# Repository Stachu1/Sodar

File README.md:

# Sodar: FPGA-Based Ultrasonic Phased Array

Sodar is a semester project exploring directional ultrasonic object detection using a custom 19-element phased array. The system combines a custom PCB, a Digilent Zedboard with Xilinx Zynq-7000 SoC, VHDL-based signal generation, C firmware running on the Zynq processing system, and a Python visualization tool.

The project was developed as a concept and experimental prototype rather than a finished sensing system. The main goals were to learn the Zynq-7000 architecture and its peripherals, investigate phased-array beam steering, and build a complete hardware-to-software signal path.

## System Overview

The system consists of four main parts:

- **19-element transmitter array** using 40 kHz piezoelectric ultrasonic transducers
- **Custom PCB** with 19 full H-bridge driver channels based on TC78H621FNG motor-driver ICs for driving the transducers
- **Digilent Zedboard (Zynq-7000 SoC)**, with VHDL logic in the programmable logic (PL) generating the phase-shifted transmit signals and C firmware running on the processing system (PS) handling acquisition and signal processing
- **Python host software** for receiving processed data over UART and visualizing the measured echo strength as a function of angle and distance

The system was able to detect a small object at distances of up to approximately 4 m when transmitting straight ahead. When steering the beam towards ±20°, the received signal became substantially weaker and more affected by noise, limiting reliable detection of the test object to approximately 1 m.

## Transducer Array

The array contains 19 identical 40 kHz ultrasonic transducers arranged in two staggered rows: one row contains 10 transducers and the other contains 9.

The physical spacing between adjacent transducers along each row is 10 mm. The second row is shifted by 5 mm, creating a staggered arrangement where the projected spacing between elements along the left-right steering axis is approximately 5 mm.

At 40 kHz, the acoustic wavelength in air is approximately 8.6 mm at room temperature, making the projected element spacing close to λ/2. The arrangement was chosen for horizontal beam steering while keeping the projected element spacing small enough to reduce unwanted grating lobes.

The array was designed for horizontal steering only; there is no intended vertical beam steering.

A 3D radiation pattern simulation was used to visualize the array's predicted transmission characteristics and beam steering performance.

## Hardware

The custom PCB contains the 19 ultrasonic transducers together with the electronics required to drive them.

Each transducer has an independent H-bridge output provided by a motor-driver IC (TC78H621FNG). The Zynq PL provides the control signals required for each channel, including an enable signal and drive-direction signals.

The board was designed, assembled, and soldered as part of the project.

Main hardware:

- Digilent ZedBoard with Xilinx Zynq-7000 SoC
- 19 - 40 kHz ultrasonic transducers
- 19 - full H-bridge driver channels
- Custom PCB with transducers and driver ICs (TC78H621FNG)
- Zynq-7000 internal XADC used for receiving the ultrasonic signal

## FPGA and Firmware

The Zynq-7000 is divided into two parts in the project:

- **Programmable Logic (PL):** VHDL implementation of the phase-controlled transmit signal generation
- **Processing System (PS):** C firmware running on the Zynq CPU for ADC acquisition, signal processing, beam control, and UART communication

### Phase-Controlled Transmit Generation

The PL contains a reusable PWM generator with programmable:

- period
- duty cycle
- phase shift

The top-level design instantiates 19 generators, with the phase of each channel calculated from the requested beam angle.

The phase of each channel is calculated from a common base phase and the channel index. This allows the relative phase between the 19 transmitters to be changed from the PS firmware without modifying the FPGA design.

The system generates 40 kHz square-wave bursts with phase offsets corresponding to the requested steering angle. The steering range used during testing was approximately -20° to +20°.

### Beam Steering

The array is steered horizontally by introducing a constant phase difference between adjacent transducers. Since the projected element spacing in the steering direction is approximately 5 mm, the required phase shift can be calculated from the wavelength of the 40 kHz ultrasonic signal.

Assuming a speed of sound of 343 m/s:

$$
\lambda = \frac{343\frac{m}{s}}{40\text{ kHz}} = 8.575\text{ mm}
$$

The phase difference between adjacent elements is then:

$$
\Delta\phi = 2\pi\frac{d}{\lambda}\sin(\theta)
$$

where $d = 5$ mm is the projected element spacing and $\theta$ is the desired steering angle.

This gives:

$$
\Delta\phi \approx 3.664\sin(\theta)\text{ rad}
$$

or, in degrees:

$$
\Delta\phi \approx 209.9\sin(\theta)^\circ
$$

The firmware therefore uses a constant of 209.9 to convert the requested steering angle into the phase difference between adjacent elements.

The calculated phase difference is converted into FPGA clock cycles and provided to the VHDL signal-generation logic. The phase of each element is then scaled according to its position in the array, producing the progressive phase shift required for beam steering.

The steering range used during testing was approximately -20° to +20°.

I'd make this section a little more detailed, because the burst-length/multiple-pulse experiments show useful engineering tradeoffs without overselling the DSP:

## Echo Acquisition and Signal Processing

The receiving transducer is sampled using the Zynq-7000's internal XADC at approximately 500 kHz.

The implemented processing pipeline:

1. XADC acquisition
2. DC offset removal
3. Absolute value
4. FIR low-pass filtering
5. Echo peak detection
6. Distance estimation

During testing, different transmit burst lengths were investigated to find a good balance between transmitted energy, echo detectability, and range resolution. In our experiments, a burst length of approximately 7 periods of the 40 kHz carrier gave the best results.

We also experimented with transmitting multiple bursts consecutively and summing the corresponding received waveforms. This provided some noise rejection by averaging out variations between individual measurements, but increased the acquisition time for each beam angle. As a result, using more bursts improved signal quality at the cost of a lower scanning refresh rate.

### DC Offset Removal

The average value of the acquired ADC buffer is calculated and subtracted from each sample. This centres the waveform approximately around zero before further processing.

### Rectification and FIR Filtering

The centred signal is passed through an absolute-value operation and then through a 30-tap FIR low-pass filter. This produces a smoothed representation of the received signal energy, making the location of the echo easier to identify.

The strongest point in the filtered signal is then used as the detected echo position.

### DC Offset Removal

The average value of the acquired ADC buffer is calculated and subtracted from each sample. This centres the waveform approximately around zero before further processing.

### Rectification and FIR Filtering

The centred signal is passed through an absolute-value operation and then through a 30-tap FIR low-pass filter. This produces a smoothed representation of the received signal energy, making the location of the echo easier to identify.

The strongest point in the filtered signal is then used as the detected echo position.

### Distance Estimation

Distance is calculated from the measured round-trip travel time using the standard ultrasonic time-of-flight relationship:

`distance = speed_of_sound × time / 2`

The speed of sound is configurable in the host-side Python script. No temperature compensation was implemented.

### Matched Filtering

Matched filtering was also investigated experimentally during development, including testing against the transmitted 40 kHz burst. It was not included in the final implemented signal-processing pipeline.

## Scanning and Object Detection

The system can scan through a range of beam angles and transmit an ultrasonic burst at each angle.

For each angle, the received signal is sampled and processed before the resulting data is sent to the host computer over UART.

A small spray-paint can placed on a flat surface in a laboratory was used as the main test object.

In straight-ahead operation, the system was able to detect the object at approximately 4 m. At larger steering angles, the received signal became weaker and noisier, with reliable detection of the same object reaching approximately 1 m around the ±20° steering range.

These results were obtained in a normal laboratory environment rather than an acoustically controlled room, so reflections and background noise were present during testing.

## Tracking Mode

An experimental tracking mode was also implemented in the PS firmware.

Instead of performing a full angular scan, the system compares the echo strength at neighbouring beam angles and moves the beam towards the stronger response.

The implementation was experimental and not sufficiently reliable to be considered a finished tracking system. It is included primarily as an experiment demonstrating how the beam-steering mechanism could be used for closed-loop object tracking.

## Host Software

The repository contains a Python script for receiving the processed data over UART and displaying it as a real-time distance-versus-angle heatmap.

The visualization represents:

- **X-axis:** beam angle
- **Y-axis:** distance
- **Colour:** measured echo strength

The Python visualization can also be used to inspect received data and experiment with parameters such as the assumed speed of sound.

## Data Format

In scan mode, the firmware transmits the processed samples for each beam angle over UART.

The implementation uses a compact hexadecimal representation containing the angle index followed by the sampled data.

The Python script contains the corresponding serial parsing and visualization code.

## Project Structure

The repository is organized into the following main components:

- `firmware/` - C firmware running on the Zynq processing system
- `hardware/` - PCB and schematic files
- `scripts/` - Python visualization and host-side tools
- `vhdl/` - VHDL source for the programmable logic
- `simulations/` - Beam-pattern simulations
- `README.md` - Project documentation

The Vivado project itself is not intended to be directly reproducible from the repository. The VHDL source is provided separately so that the hardware logic can be inspected without including the generated Vivado project files.

## Results and Limitations

The prototype demonstrated the basic principle of electronically steering an ultrasonic phased array and detecting echoes from a physical object.

The main experimental results were:

| Configuration | Approximate result |
|---|---:|
| Straight-ahead detection | Up to ~4 m |
| Beam steering | -20° to +20° |
| Detection at large steering angles | Up to ~1 m |
| Transmit frequency | 40 kHz |
| Number of transmit elements | 19 |
| ADC sampling rate | ~500 kHz |
| FIR filter | 30 taps |

The system was a semester project and has several limitations. In particular, the received signal became significantly weaker as the beam was steered away from the centre, limiting the useful detection range. The tracking mode was also experimental rather than a robust tracking system.

The project was primarily intended as a proof-of-concept and learning exercise rather than as a finished ultrasonic sensing platform.

## What I Learned

The project provided practical experience with several parts of a mixed hardware/software system:

- Designing and assembling a relatively high-channel-count custom PCB
- Driving 19 ultrasonic transducers using independent H-bridge channels
- Developing VHDL logic for precisely phase-shifted signal generation
- Working with the Zynq-7000 PS/PL architecture
- Acquiring signals using the Zynq's internal XADC
- Implementing basic real-time signal processing in C
- Communicating processed measurements to a PC over UART
- Simulating and experimentally testing phased-array beam patterns
- Investigating the practical limitations of ultrasonic beam steering

The project was developed as a second-year engineering project, and the prototype left several areas open for further development, including improved analogue signal conditioning, more robust echo detection, better calibration of the array, and improved performance at larger steering angles. A natural next step for the signal processing would be to transmit a frequency-modulated chirp and use matched filtering on the received signal, which could improve range resolution and provide better noise immunity compared with the simple burst and peak-detection approach used in the prototype.

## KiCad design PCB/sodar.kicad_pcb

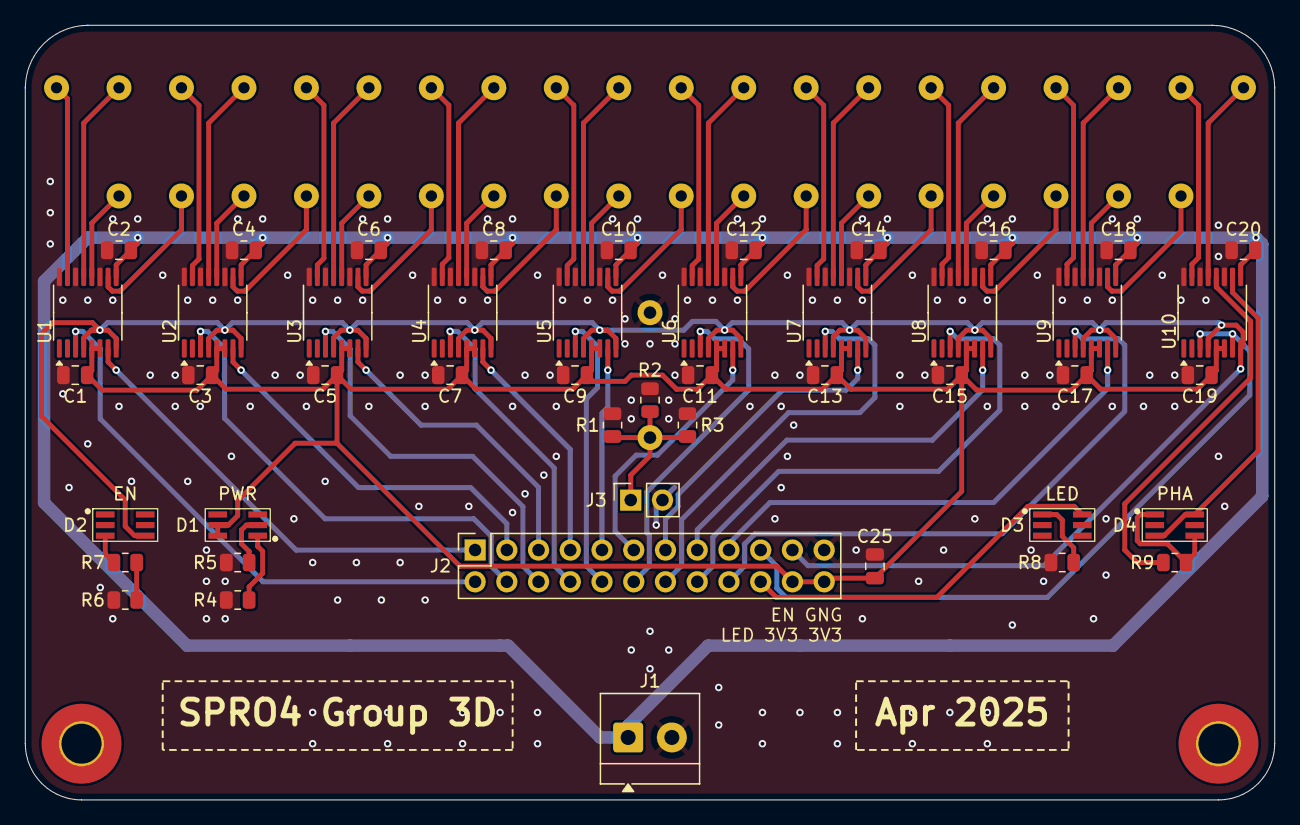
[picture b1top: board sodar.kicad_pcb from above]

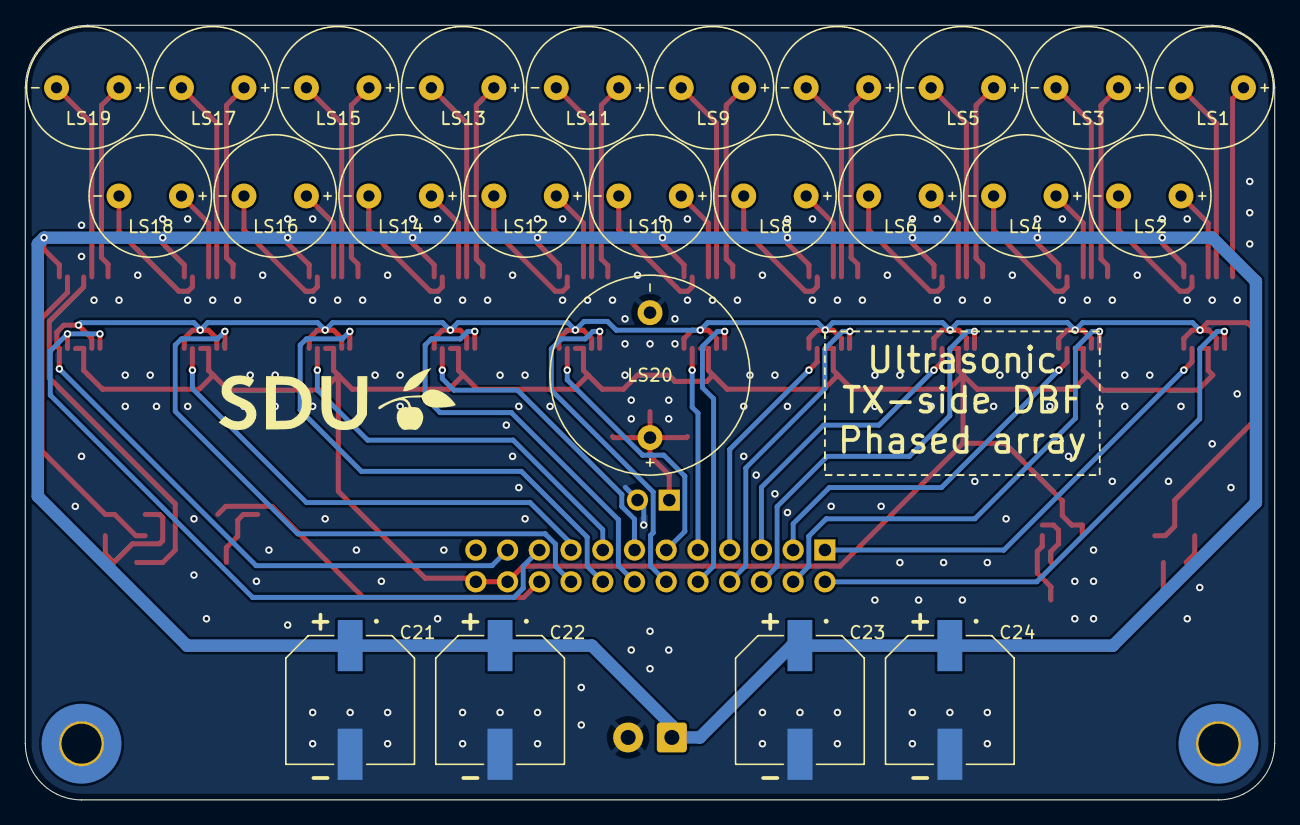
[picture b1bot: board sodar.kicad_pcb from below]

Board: 2 copper layers, 100.0 x 62.0 mm, 73 parts (24 on the bottom side), 71 nets.

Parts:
C1, C2, C3, C4, C5, C6, C7, C8, C9, C10, C11, C12, C13, C14, C15, C16, C17, C18, C19, C20: 100n; C_0805_2012Metric
C21, C22, C23, C24: 560u; CAP_EEEFT1V561AP
C25: 10u; C_0805_2012Metric
D1, D2, D3, D4: QBLP680-RGB1
J1: Screw_Terminal_01x02; TerminalBlock_4Ucon_1x02_P3.50mm_Horizontal
J2: Conn_02x12_Counter_Clockwise; PinSocket_2x12_P2.54mm_Vertical
J3: Conn_01x02; PinSocket_1x02_P2.54mm_Vertical
LS1, LS2, LS3, LS4, LS5, LS6, LS7, LS8, LS9, LS10, LS11, LS12, LS13, LS14, LS15, LS16, LS17, LS18, LS19: Speaker_Ultrasound; CUSA-T80-15-2400-TH
LS20: Speaker_Ultrasound; MCUSR16A39S12RO
MountingHole1, MountingHole2: MountingHole_3.2mm_M3_Pad_TopBottom
R1: 100k; R_0805_2012Metric
R2: 51k; R_0805_2012Metric
R3: 20k; R_0805_2012Metric
R4, R5, R8: 43; R_0805_2012Metric
R6, R7: 100; R_0805_2012Metric
R9: 2k; R_0805_2012Metric
U1, U2, U3, U4, U5, U6, U7, U8, U9, U10: TC78H621FNG; TSSOP-16_4.4x5mm_P0.65mm

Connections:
+3V3: C1.1, C3.1, C5.1, C7.1, C9.1, C11.1, C13.1, C15.1, C17.1, C19.1, C25.1, D1.5 (G+), D1.6 (B+), J2.22, J2.24, U1.5 (VCC), U1.6 (/STBY), U2.5 (VCC), U2.6 (/STBY), U3.5 (VCC), U3.6 (/STBY), U4.5 (VCC), U4.6 (/STBY), U5.5 (VCC), U5.6 (/STBY), U6.5 (VCC), U6.6 (/STBY), U7.5 (VCC), U7.6 (/STBY), U8.5 (VCC), U8.6 (/STBY), U9.5 (VCC), U9.6 (/STBY), U10.5 (VCC), U10.6 (/STBY)
EN: D2.4 (R+), J2.21, U1.4 (EN_A), U1.8 (EN_B), U2.4 (EN_A), U2.8 (EN_B), U3.4 (EN_A), U3.8 (EN_B), U4.4 (EN_A), U4.8 (EN_B), U5.4 (EN_A), U5.8 (EN_B), U6.4 (EN_A), U6.8 (EN_B), U7.4 (EN_A), U7.8 (EN_B), U8.4 (EN_A), U8.8 (EN_B), U9.4 (EN_A), U9.8 (EN_B), U10.4 (EN_A), U10.8 (EN_B)
GND: C1.2, C2.1, C3.2, C4.1, C5.2, C6.1, C7.2, C8.1, C9.2, C10.1, C11.2, C12.1, C13.2, C14.1, C15.2, C16.1, C17.2, C18.1, C19.2, C20.1, C21.2, C22.2, C23.2, C24.2, C25.2, J1.2, J2.23, J3.2, LS20.2, R1.2, R2.2, R3.2, R4.1, R5.1, R6.1, R8.1, U1.11 (GND), U1.14 (GND), U1.16 (GND), U2.11 (GND), U2.14 (GND), U2.16 (GND), U3.11 (GND), U3.14 (GND), U3.16 (GND), U4.11 (GND), U4.14 (GND), U4.16 (GND), U5.11 (GND), U5.14 (GND), U5.16 (GND), U6.11 (GND), U6.14 (GND), U6.16 (GND), U7.11 (GND), U7.14 (GND), U7.16 (GND), U8.11 (GND), U8.14 (GND), U8.16 (GND), U9.11 (GND), U9.14 (GND), U9.16 (GND), U10.11 (GND), U10.14 (GND), U10.16 (GND)
LED: D3.6 (B+), J2.20
unnamed: D1.1 (B-), R4.2
unnamed: D1.2 (G-), R5.2
unnamed: D2.3 (R-), R7.2
unnamed: D3.1 (B-), R8.2
unnamed: D4.1 (B-), D4.4 (R+), R9.2
unnamed: R6.2, R7.1
unnamed: LS1.1, U1.15 (AO1)
unnamed: LS1.2, U1.13 (AO2)
unnamed: LS2.1, U1.12 (BO1)
unnamed: LS2.2, U1.10 (BO2)
unnamed: LS3.1, U2.15 (AO1)
unnamed: LS3.2, U2.13 (AO2)
unnamed: LS4.1, U2.12 (BO1)
unnamed: LS4.2, U2.10 (BO2)
unnamed: LS5.1, U3.15 (AO1)
unnamed: LS5.2, U3.13 (AO2)
unnamed: LS6.1, U3.12 (BO1)
unnamed: LS6.2, U3.10 (BO2)
unnamed: LS7.1, U4.15 (AO1)
unnamed: LS7.2, U4.13 (AO2)
unnamed: LS8.1, U4.12 (BO1)
unnamed: LS8.2, U4.10 (BO2)
unnamed: LS9.1, U5.15 (AO1)
unnamed: LS9.2, U5.13 (AO2)
unnamed: LS10.1, U5.12 (BO1)
unnamed: LS10.2, U5.10 (BO2)
unnamed: LS11.1, U6.15 (AO1)
unnamed: LS11.2, U6.13 (AO2)
unnamed: LS12.1, U6.12 (BO1)
unnamed: LS12.2, U6.10 (BO2)
unnamed: LS13.1, U7.15 (AO1)
unnamed: LS13.2, U7.13 (AO2)
unnamed: LS14.1, U7.12 (BO1)
unnamed: LS14.2, U7.10 (BO2)
unnamed: LS15.1, U8.15 (AO1)
unnamed: LS15.2, U8.13 (AO2)
unnamed: LS16.1, U8.12 (BO1)
unnamed: LS16.2, U8.10 (BO2)
unnamed: LS17.1, U9.15 (AO1)
unnamed: LS17.2, U9.13 (AO2)
unnamed: LS18.1, U9.12 (BO1)
unnamed: LS18.2, U9.10 (BO2)
unnamed: LS19.1, U10.15 (AO1)
unnamed: LS19.2, U10.13 (AO2)
PHA_LED1: R9.1, U10.12 (BO1)
PHA_LED2: D4.3 (R-), D4.6 (B+), U10.10 (BO2)
RX: J3.1, LS20.1, R1.1, R2.1, R3.1
S1: J2.2, U1.3 (PHA_A)
S2: J2.1, U1.7 (PHA_B)
S3: J2.4, U2.3 (PHA_A)
S4: J2.3, U2.7 (PHA_B)
S5: J2.6, U3.3 (PHA_A)
S6: J2.5, U3.7 (PHA_B)
S7: J2.8, U4.3 (PHA_A)
S8: J2.7, U4.7 (PHA_B)
S9: J2.10, U5.3 (PHA_A)
S10: J2.9, U5.7 (PHA_B)
S11: J2.12, U6.3 (PHA_A)
S12: J2.11, U6.7 (PHA_B)
S13: J2.14, U7.3 (PHA_A)
S14: J2.13, U7.7 (PHA_B)
S15: J2.16, U8.3 (PHA_A)
S16: J2.15, U8.7 (PHA_B)
S17: J2.18, U9.3 (PHA_A)
S18: J2.17, U9.7 (PHA_B)
S19: J2.19, U10.3 (PHA_A), U10.7 (PHA_B)
Vdrive: C2.2, C4.2, C6.2, C8.2, C10.2, C12.2, C14.2, C16.2, C18.2, C20.2, C21.1, C22.1, C23.1, C24.1, J1.1, U1.9 (VM), U2.9 (VM), U3.9 (VM), U4.9 (VM), U5.9 (VM), U6.9 (VM), U7.9 (VM), U8.9 (VM), U9.9 (VM), U10.9 (VM)

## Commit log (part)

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2025-04-10 Inital commit
2025-04-10 Added components footprints & symbols
2025-04-10 Renamed files
2025-04-10 Redo the project and added TC78H621FNG sym & footprint
2025-04-10 Added waterfall_plot.py
2025-04-10 added plot python
2025-04-10 Added gitignore
2025-04-10 Removed ignored files & moved scripts to scripts folder
2025-04-10 Added Receiver & LED components
2025-04-10 Wired first driver-tansducer module
2025-04-10 vhdl and sdk code for the 19 phase shifted pwm
2025-04-11 added second transducer module
2025-04-11 Added the remaining drivers & transducer to the schematics
2025-04-11 Added new cap footprint
2025-04-11 Added capacitors to the drivers & Added receiver
2025-04-11 Added Pin header
2025-04-11 Updated symbols' bg
2025-04-11 Added LEDs to the schematics - PWR EN STBY LED PHA
2025-04-11 Updated gitignore
2025-04-11 Added Screw terminal & capacitors to the schematics
2025-04-11 Assigned footprints
2025-04-11 Fixed receiver schematics
2025-04-11 Updated transducers footprints - pad numbers & silkscreen
2025-04-11 Init PCB
2025-04-13 updated transmiter footprint
2025-04-13 Moved the transducers and the drivers in the right positions
2025-04-13 first PCB layout finished, to be reviewed
2025-04-13 Szymi pcb design (#5)
    * updated transmiter footprint
    * Moved the transducers and the drivers in the right positions
    * first PCB layout finished, to be reviewed
    ---------
2025-04-13 Sodar plot for +/- 30 deg & 500 samples
2025-04-14 My idea of designe with placement change and begin of connections
2025-04-14 Moved driver ICs
2025-04-15 Added a bulk cap on 3V3 line
2025-04-15 Better decoupling caps placement
2025-04-15 Routed transducers and decoup caps to the ICs
2025-04-15 Moved signal connections on the header for easier routing
2025-04-15 Routed signal lines from the headero to the driver ICs
2025-04-15 Improved signal routing & routed receiver pull-down resistors
2025-04-15 Thicker REF text & centered
2025-04-15 Movec components & connected STBY signal
2025-04-15 Better STBY routing & Started to route EN
2025-04-15 First version routing of EN, STBY, Transducers, 3.3V and Vdrive
2025-04-15 Added mounting holes
2025-04-15 connected all and fixed all of the errors
2025-04-15 Changed some traces and led possiotion
2025-04-15 Added cap on 3.3V and changed the place for a vdrive and rerouted nececery things
2025-04-16 Routed EN
2025-04-16 Moved the header 2mm lower so that there is space for the receiver
2025-04-16 some routing changes
2025-04-16 Rerouted STBY to 3V3 as we set it to 3V3 anyway
2025-04-16 Routed 3V3/STBY
2025-04-16 Routed EN on the back for better caps routing
2025-04-16 Routed VDrvie screw terminal & caps
2025-04-16 Added .DS_store to .gitignore
2025-04-16 Finished VDrive route & LEDs
2025-04-16 PCB sphape changes & DRC fixes
2025-04-16 Added moting holes and copper filed zone
2025-04-16 DRC fixes & Stitching vias
2025-04-16 Moved LEDs to the sides
2025-04-17 Improved PHA signal routing
2025-04-17 Anotehr routing improvement
2025-04-17 Don't ignore footprint stuff in the DRC
2025-04-17 More vias
2025-04-17 Added pin description & SPRO4 Group4 text
2025-04-17 Added SDU logo to the footprints
2025-04-17 Added some silkscreen details
2025-04-27 added sdk c code
2025-04-27 Added vhdl code
2025-04-27 turn it on
2025-04-27 Added constrain file
2025-04-29 Changed sdk c code for updated
2025-05-01 Updated gitignore for vivado project
2025-05-01 Added vivado files?
2025-05-01 IDK it works on my laptop but doesn't work for anyone else
2025-05-01 Added ps side firmware
2025-05-01 Updated scripts for faster baud rate
2025-05-01 Added TRK mode but it's not working great
2025-05-08 Changed FOV to 40deg & added auto scaling
2025-05-08 Read data and plot in different threads for highier refresh rate
2025-05-08 Added FOV macro & optimal transmit settings
2025-05-14 Ps firmware (#8)
    * Added ps side firmware
    * Updated scripts for faster baud rate
    * Added TRK mode but it's not working great
    * Changed FOV to 40deg & added auto scaling
    * Read data and plot in different threads for highier refresh rate
    * Added FOV macro & optimal transmit settings
2025-05-29 Added VHDL code zip
2025-05-29 Added different version of VHDL code zip
2025-05-29 Added udpated VHDL code zip
2025-05-30 Deleted archive summary
2025-07-10 Update README.md (#10)
2025-09-26 Add example setup section with images
    Added example setup images to the README.
